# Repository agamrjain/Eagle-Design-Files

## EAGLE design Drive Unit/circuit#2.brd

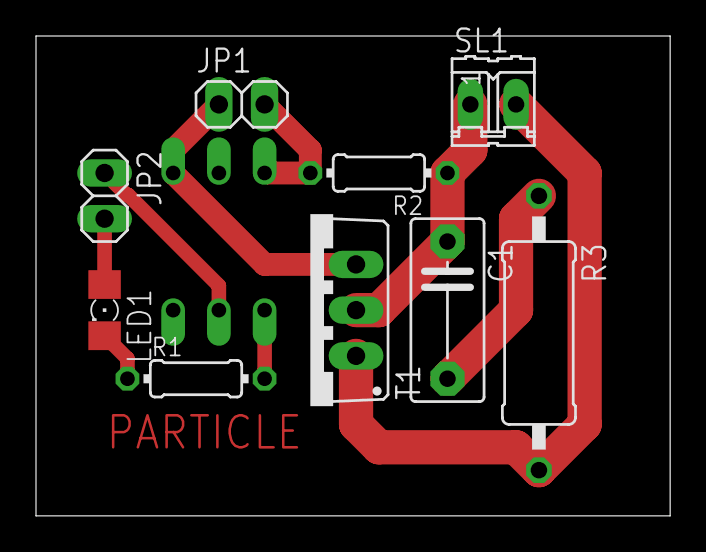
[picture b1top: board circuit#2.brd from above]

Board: 2 copper layers, 35.2 x 26.7 mm, 10 parts (1 on the bottom side), 9 nets.

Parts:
C1: C7.5B4
JP1, JP2: 1X02
LED1: LED_1206
OK1: MOC3011M; DIL06
R1, R2: 0204/7
R3: 0411/15
SL1: 02P
T1: BT138-V; TO220BV

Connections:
unnamed: LED1.C, R1.1
unnamed: OK1.1, R1.2
unnamed: JP2.2, LED1.A
unnamed: JP2.1, OK1.2
unnamed: JP1.2, OK1.6, R2.2
unnamed: JP1.1, OK1.4, T1.G
unnamed: R3.2, SL1.2, T1.T1
unnamed: C1.2, R3.1
unnamed: C1.1, R2.1, SL1.1, T1.T2
